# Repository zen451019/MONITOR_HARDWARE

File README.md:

# NEMO: Electromechanical Monitoring Firmware

This repository contains the complete source code for the firmware for NEMO (Node for Electromechanical Monitoring & Operation), a high-performance IoT node designed for real-time monitoring of analog signals.

The system is optimized to capture, process, and transmit voltage and current data from sensors, making it an ideal solution for predictive maintenance, energy consumption monitoring, and industrial machinery diagnostics applications.

## Modbus master monitor documentation

English
https://zen451019.github.io/MONITOR_HARDWARE/28-11-25/English/MASTER_MODBUS/html/index.html

Spanish
https://zen451019.github.io/MONITOR_HARDWARE/28-11-25/Español/MASTER_MODBUS/html/index.html

## Modbus slave monitor documentation
English
https://zen451019.github.io/MONITOR_HARDWARE/28-11-25/English/SLAVE_MODBUS/html/index.html

Spanish
https://zen451019.github.io/MONITOR_HARDWARE/28-11-25/Español/SLAVE_MODBUS/html/index.html

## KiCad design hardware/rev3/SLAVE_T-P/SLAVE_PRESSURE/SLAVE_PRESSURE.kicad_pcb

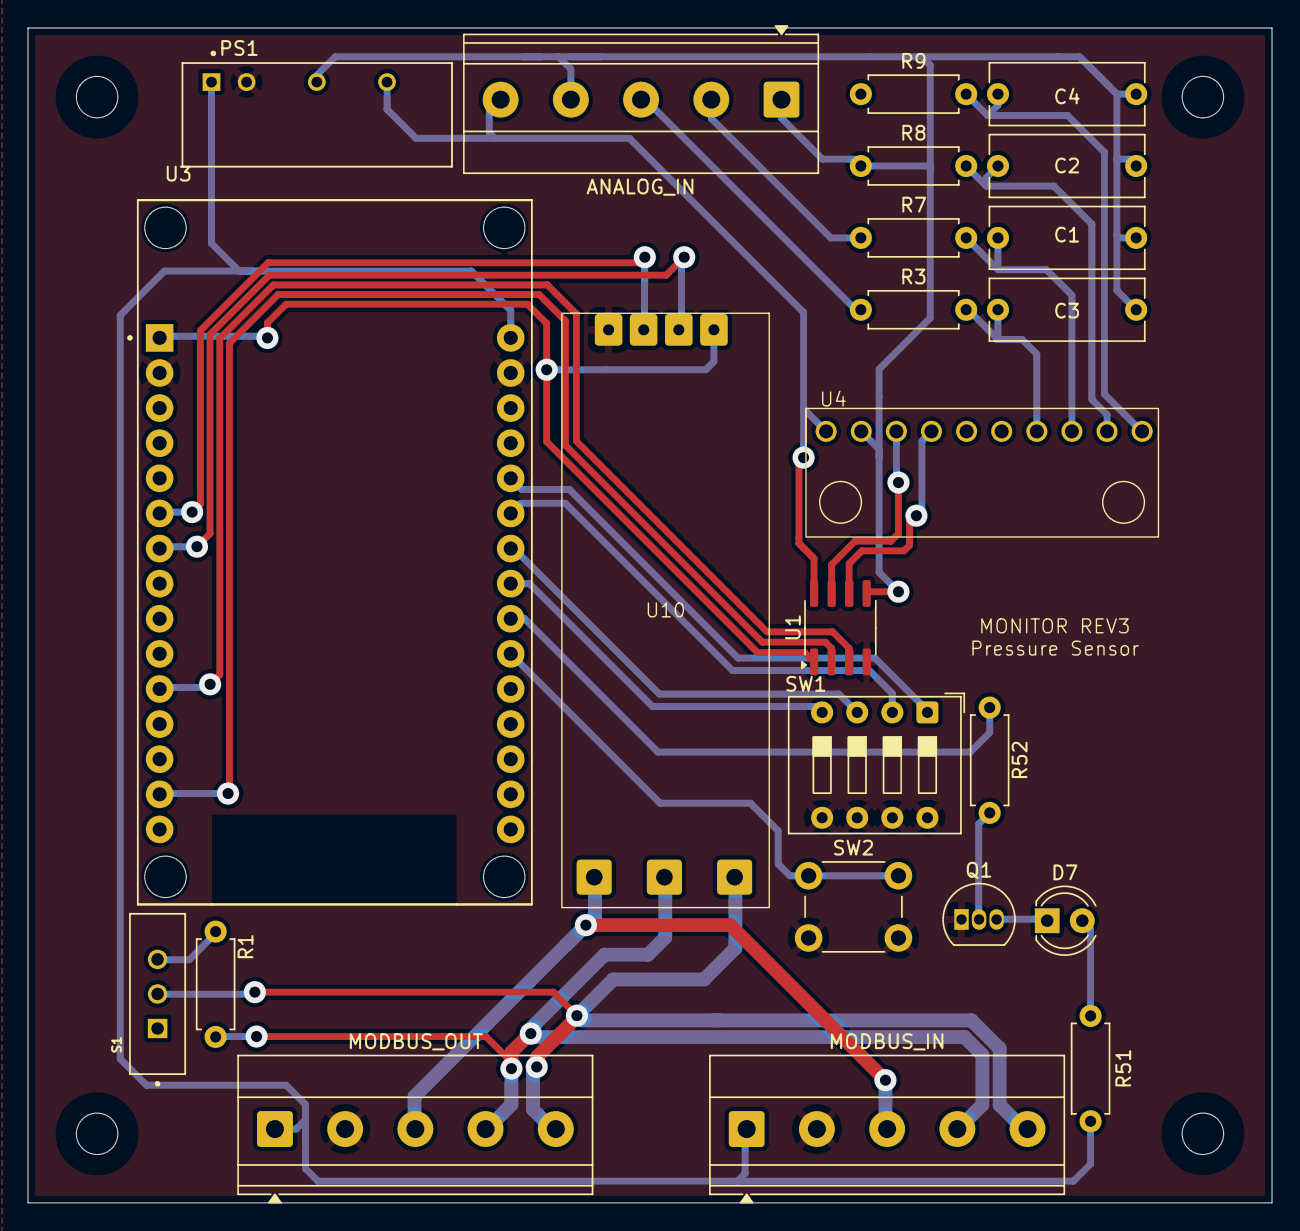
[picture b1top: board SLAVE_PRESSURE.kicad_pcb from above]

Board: 2 copper layers, 90.0 x 85.0 mm, 24 parts (0 on the bottom side), 31 nets.

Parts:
ANALOG_IN: SCREW_TERMINAL_5; TerminalBlock_Phoenix_MKDS-1,5-5-5.08_1x05_P5.08mm_Horizont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
C1, C2, C3, C4: 100nF; C_Rect_L11.0mm_W4.3mm_P10.00mm_MKT
D7: LED; LED_D4.0mm
MODBUS_IN: SCREW_TERMINAL_5; TerminalBlock_Phoenix_MKDS-1,5-5-5.08_1x05_P5.08mm_Horizont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
MODBUS_OUT: SCREW_TEMINAL_5; TerminalBlock_Phoenix_MKDS-1,5-5-5.08_1x05_P5.08mm_Horizont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
PS1: TMH_0505S; CONV_TMH_0505S
Q1: PN2222A; TO-92_Inline
R1, R51: 330; R_Axial_DIN0207_L6.3mm_D2.5mm_P7.62mm_Horizontal
R3, R7, R8, R9: 1K; R_Axial_DIN0207_L6.3mm_D2.5mm_P7.62mm_Horizontal
R52: 3.3k; R_Axial_DIN0207_L6.3mm_D2.5mm_P7.62mm_Horizontal
S1: MINI-SPDT-SW; SW_MINI-SPDT-SW
SW1: SW_DIP_x04; SW_DIP_SPSTx04_Slide_9.78x12.34mm_W7.62mm_P2.54mm
SW2: SW_Push; SW_PUSH_6mm
U1: ADuM1201AR; SOIC-8_3.9x4.9mm_P1.27mm
U3: ESP32-DEVKIT-V1; MODULE_ESP32_DEVKIT_V1
U4: ADS1015
U10: RS485_TRANSCEIVER; XY-017

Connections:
3V3: U1.1 (VDD1), U3.1 (3V3), U10.1 (VCC)
5V: MODBUS_IN.1, MODBUS_OUT.1, PS1.1 (+VIN(VCC)), R51.1, U3.30 (VIN)
5V_ISO: ANALOG_IN.5, PS1.6 (+VOUT), U1.8 (VDD2), U4.8 (VDD)
485+: MODBUS_IN.5, MODBUS_OUT.5, S1.2, U10.5 (A)
485-: MODBUS_IN.4, MODBUS_OUT.4, R1.2, U10.6 (B)
BUTTOM: SW2.1, U3.21 (D32)
DIP_1: SW1.1, U3.26 (D14)
DIP_2: SW1.2, U3.25 (D27)
DIP_3: SW1.3, U3.24 (D26)
DIP_4: SW1.4, U3.23 (D25)
GND: MODBUS_IN.2, MODBUS_OUT.2, PS1.2 (-VIN(GND)), Q1.1 (E), SW1.5, SW1.6, SW1.7, SW1.8, SW2.2, U1.4 (GND1), U3.2 (GND), U3.29 (GND), U10.4 (GND)
GND_ISO: ANALOG_IN.4, C1.1, C2.1, C3.1, C4.1, PS1.4 (-VOUT), U1.5 (GND2), U4.3 (GND)
GND_T: MODBUS_IN.3, MODBUS_OUT.3, U10.7 (GND)
LED: R52.2, U3.22 (D33)
unnamed: D7.2 (A), R51.2
unnamed: D7.1 (K), Q1.3 (C)
unnamed: Q1.2 (B), R52.1
unnamed: R1.1, S1.3
RX: U3.6 (RX2), U10.3 (RXD)
SCL: U1.2 (VOA), U3.14 (D22)
SCL_H: U1.7 (VIA), U4.10 (SCL)
SDA: U1.3 (VIB), U3.11 (D21)
SDA_H: U1.6 (VOB), U4.9 (SDA)
SIGNAL_1: ANALOG_IN.3, R3.1
SIGNAL_2: ANALOG_IN.2, R7.1
SIGNAL_3: ANALOG_IN.1, R8.1
SIGNAL_OUT1: C3.2, R3.2, U4.4 (AIN0)
SIGNAL_OUT2: C1.2, R7.2, U4.5 (AIN1)
SIGNAL_OUT3: C2.2, R8.2, U4.6 (AIN2)
SIGNAL_OUT4: C4.2, R9.2, U4.7 (AIN3)
TX: U3.7 (TX2), U10.2 (TXD)

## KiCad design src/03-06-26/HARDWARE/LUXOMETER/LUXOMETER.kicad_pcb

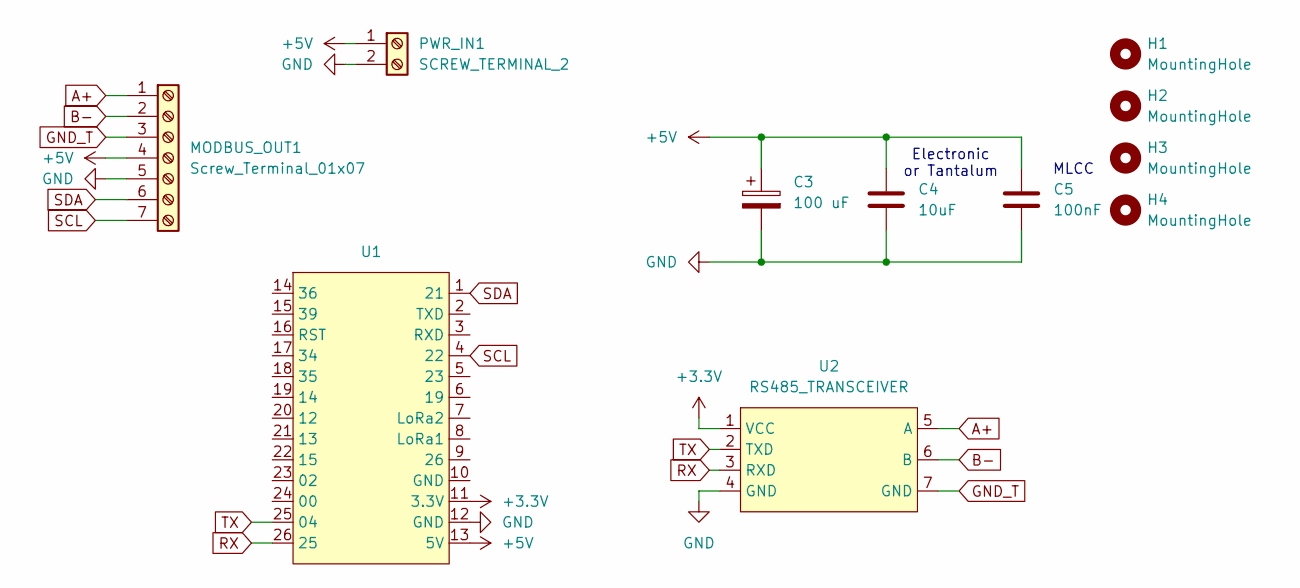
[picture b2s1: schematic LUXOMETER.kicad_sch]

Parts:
C3: 100 uF; CP_Radial_D8.0mm_P5.00mm
C4: 10uF; C_Disc_D7.5mm_W5.0mm_P5.00mm
C5: 100nF; C_Disc_D5.0mm_W2.5mm_P2.50mm
H1, H2, H3, H4: MountingHole; MountingHole_3.2mm_M3
MODBUS_OUT1: Screw_Terminal_01x07; TerminalBlock_Phoenix_MKDS-1,5-7-5.08_1x07_P5.08mm_Horizont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
PWR_IN1: SCREW_TERMINAL_2; TerminalBlock_Phoenix_MKDS-1,5-2-5.08_1x02_P5.08mm_Horizont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
U1: ttgo_lora32
U2: RS485_TRANSCEIVER; XY-017

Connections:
+3.3V: U1.11 (3.3V), U2.1 (VCC)
+5V: C3.1, C4.1, C5.1, MODBUS_OUT1.4, PWR_IN1.1, U1.13 (5V)
A+: MODBUS_OUT1.1, U2.5 (A)
B-: MODBUS_OUT1.2, U2.6 (B)
GND: C3.2, C4.2, C5.2, MODBUS_OUT1.5, PWR_IN1.2, U1.12 (GND), U2.4 (GND)
GND_T: MODBUS_OUT1.3, U2.7 (GND)
RX: U1.26 (25), U2.3 (RXD)
SCL: MODBUS_OUT1.7, U1.4 (22)
SDA: MODBUS_OUT1.6, U1.1 (21)
TX: U1.25 (04), U2.2 (TXD)

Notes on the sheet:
Electronic or Tantalum
MLCC

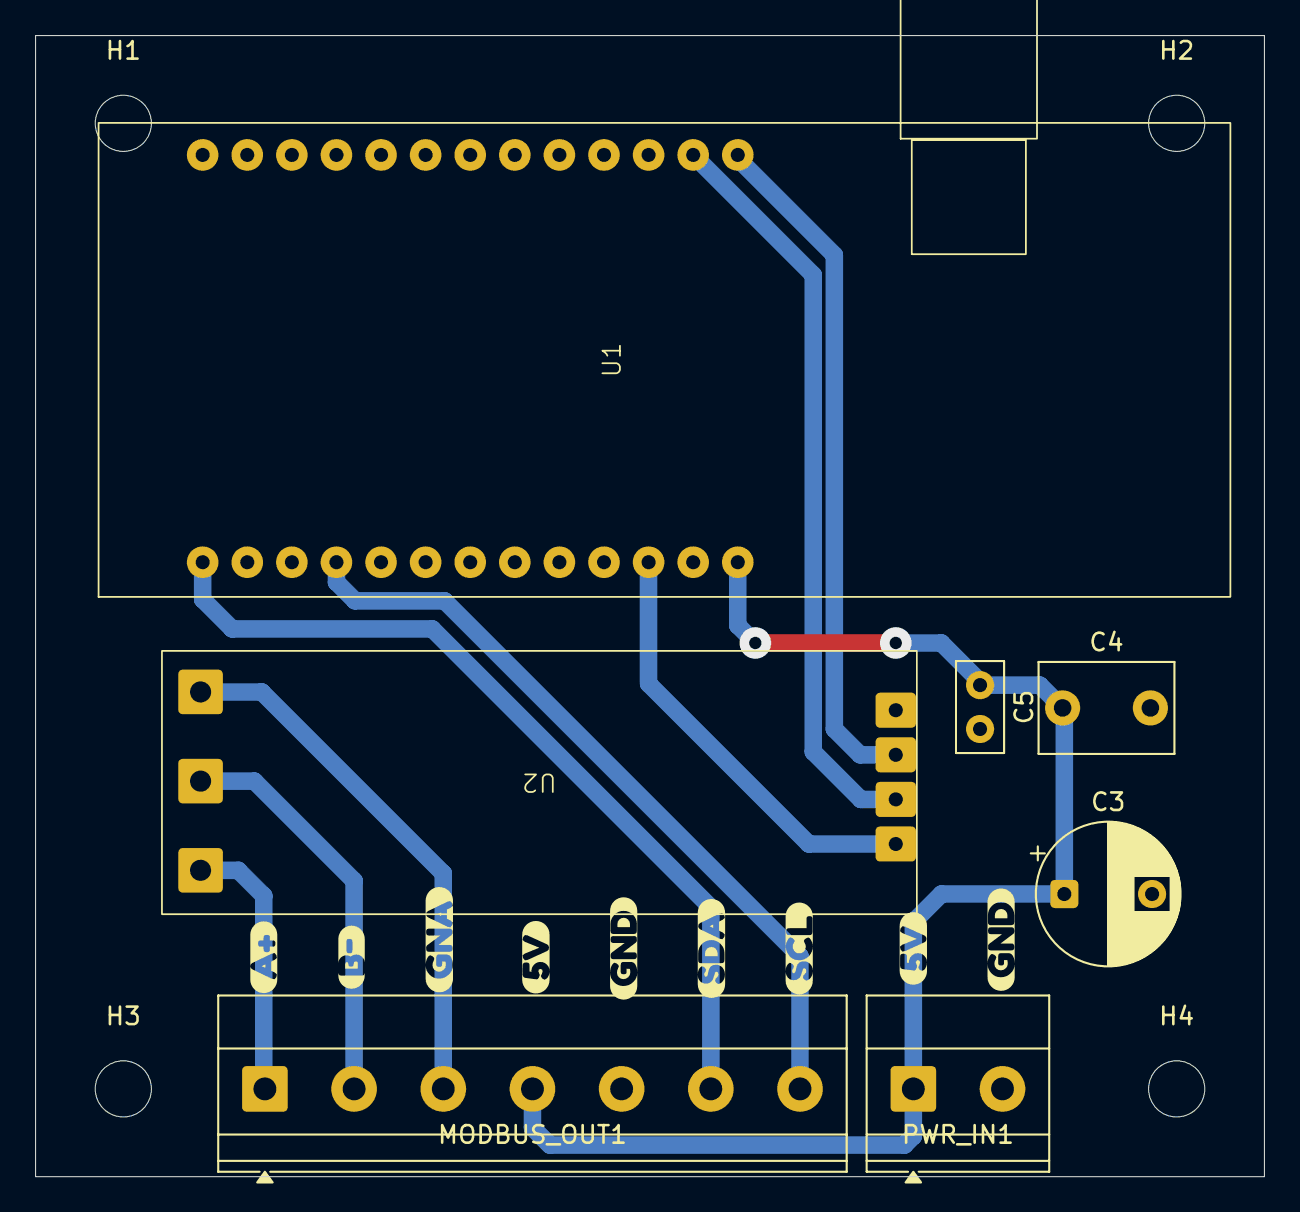
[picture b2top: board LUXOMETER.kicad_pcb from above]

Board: 2 copper layers, 70.0 x 65.0 mm, 20 parts (0 on the bottom side), 10 nets.

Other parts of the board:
kibuzzard-6A2423AA: G***; kibuzzard-6A2423AA
kibuzzard-6A2423C2: G***; kibuzzard-6A2423C2
kibuzzard-6A2424E2: G***; kibuzzard-6A2424E2
kibuzzard-6A2424EE, kibuzzard-6A2424EE#2: G***; kibuzzard-6A2424EE
kibuzzard-6A2424FA, kibuzzard-6A2424FA#2: G***; kibuzzard-6A2424FA
kibuzzard-6A24251B: G***; kibuzzard-6A24251B
kibuzzard-6A24252A: G***; kibuzzard-6A24252A

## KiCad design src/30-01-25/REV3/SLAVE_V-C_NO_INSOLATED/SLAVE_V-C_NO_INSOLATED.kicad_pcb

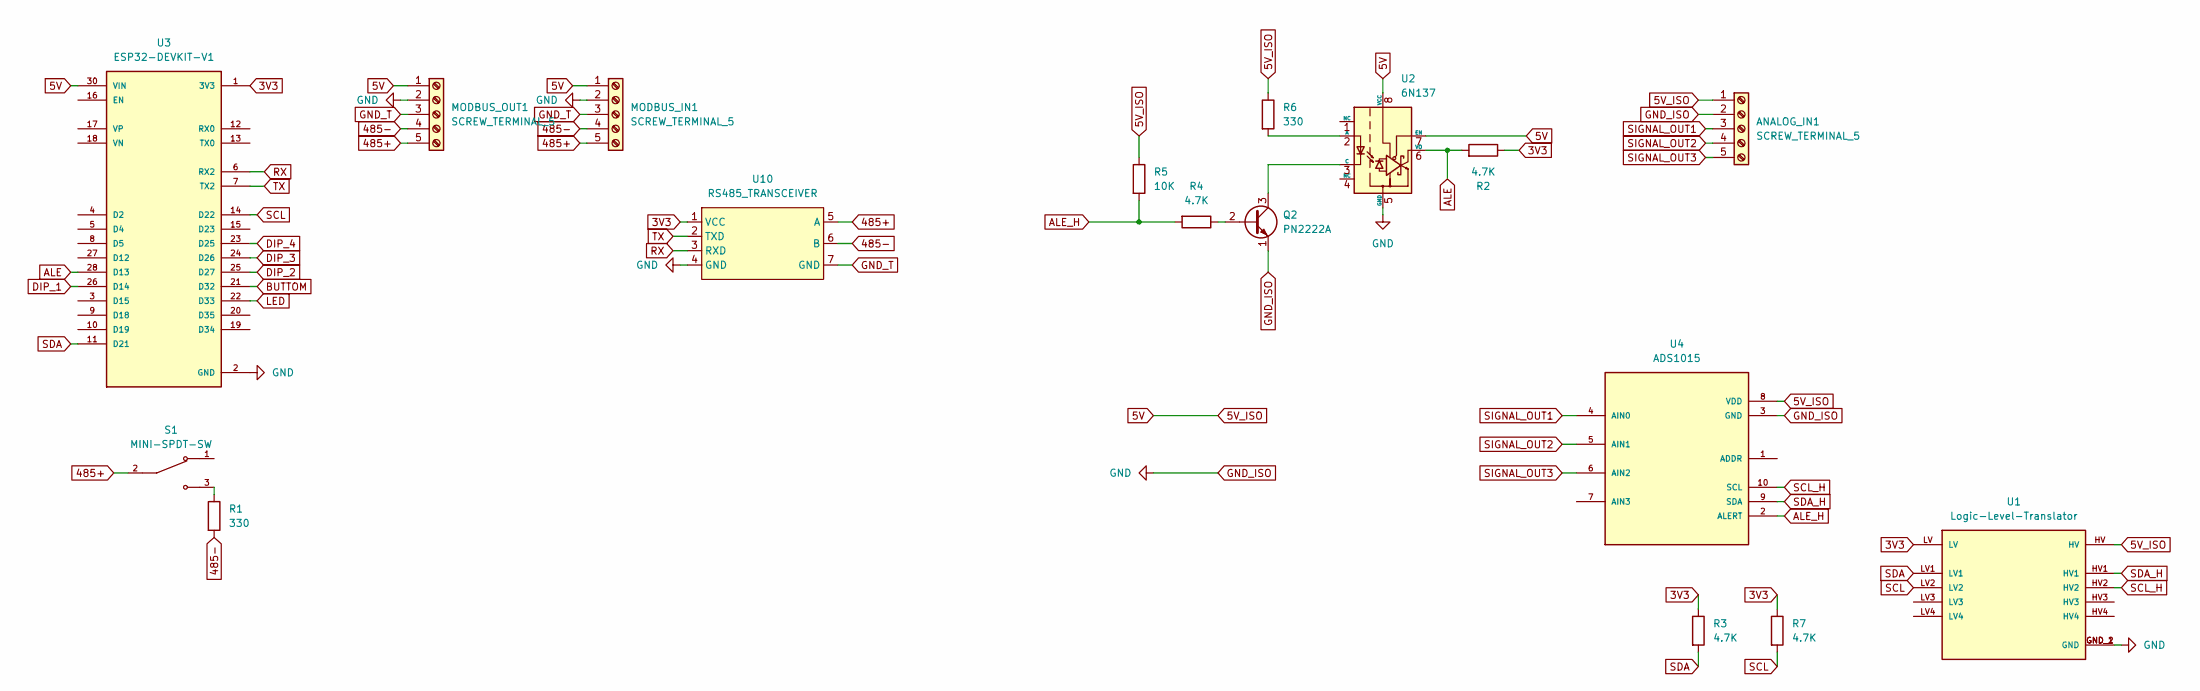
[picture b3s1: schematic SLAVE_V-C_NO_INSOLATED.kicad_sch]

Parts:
ANALOG_IN1: SCREW_TERMINAL_5; TerminalBlock_Phoenix_MKDS-1,5-5-5.08_1x05_P5.08mm_Horizont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
MODBUS_IN1: SCREW_TERMINAL_5; TerminalBlock_Phoenix_MKDS-1,5-5-5.08_1x05_P5.08mm_Horizont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
MODBUS_OUT1: SCREW_TERMINAL_5; TerminalBlock_Phoenix_MKDS-1,5-5-5.08_1x05_P5.08mm_Horizont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
Q2: PN2222A; TO-92_Inline
R1, R6: 330; R_Axial_DIN0207_L6.3mm_D2.5mm_P7.62mm_Horizontal
R2, R3, R4, R7: 4.7K; R_Axial_DIN0207_L6.3mm_D2.5mm_P7.62mm_Horizontal
R5: 10K; R_Axial_DIN0207_L6.3mm_D2.5mm_P7.62mm_Horizontal
S1: MINI-SPDT-SW; SW_MINI-SPDT-SW
U1: Logic-Level-Translator; CONV_BOB-12009
U2: 6N137; DIP-8_W7.62mm
U3: ESP32-DEVKIT-V1; MODULE_ESP32_DEVKIT_V1; PARTREV N/A
U4: ADS1015
U10: RS485_TRANSCEIVER; XY-017

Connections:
3V3: R2.1, R3.1, R7.1, U1.LV, U3.1 (3V3), U10.1 (VCC)
5V: ANALOG_IN1.1, MODBUS_IN1.1, MODBUS_OUT1.1, R5.1, R6.1, U1.HV, U2.7 (EN), U2.8 (VCC), U3.30 (VIN), U4.8 (VDD)
485+: MODBUS_IN1.5, MODBUS_OUT1.5, S1.2, U10.5 (A)
485-: MODBUS_IN1.4, MODBUS_OUT1.4, R1.2, U10.6 (B)
ALE: R2.2, U2.6 (VO), U3.28 (D13)
ALE_H: R4.2, R5.2, U4.2 (ALERT)
BUTTOM: U3.21 (D32)
DIP_1: U3.26 (D14)
DIP_2: U3.25 (D27)
DIP_3: U3.24 (D26)
DIP_4: U3.23 (D25)
GND_ISO: ANALOG_IN1.2, MODBUS_IN1.2, MODBUS_OUT1.2, Q2.1 (E), U1.GND_1 (GND), U1.GND_2 (GND), U2.5 (GND), U3.2 (GND), U3.29 (GND), U4.3 (GND), U10.4 (GND)
GND_T: MODBUS_IN1.3, MODBUS_OUT1.3, U10.7 (GND)
LED: U3.22 (D33)
unnamed: Q2.2 (B), R4.1
unnamed: Q2.3 (C), U2.3 (C)
unnamed: R1.1, S1.3
unnamed: R6.2, U2.2 (A)
RX: U3.6 (RX2), U10.3 (RXD)
SCL: R7.2, U1.LV2, U3.14 (D22)
SCL_H: U1.HV2, U4.10 (SCL)
SDA: R3.2, U1.LV1, U3.11 (D21)
SDA_H: U1.HV1, U4.9 (SDA)
SIGNAL_OUT1: ANALOG_IN1.3, U4.4 (AIN0)
SIGNAL_OUT2: ANALOG_IN1.4, U4.5 (AIN1)
SIGNAL_OUT3: ANALOG_IN1.5, U4.6 (AIN2)
TX: U3.7 (TX2), U10.2 (TXD)

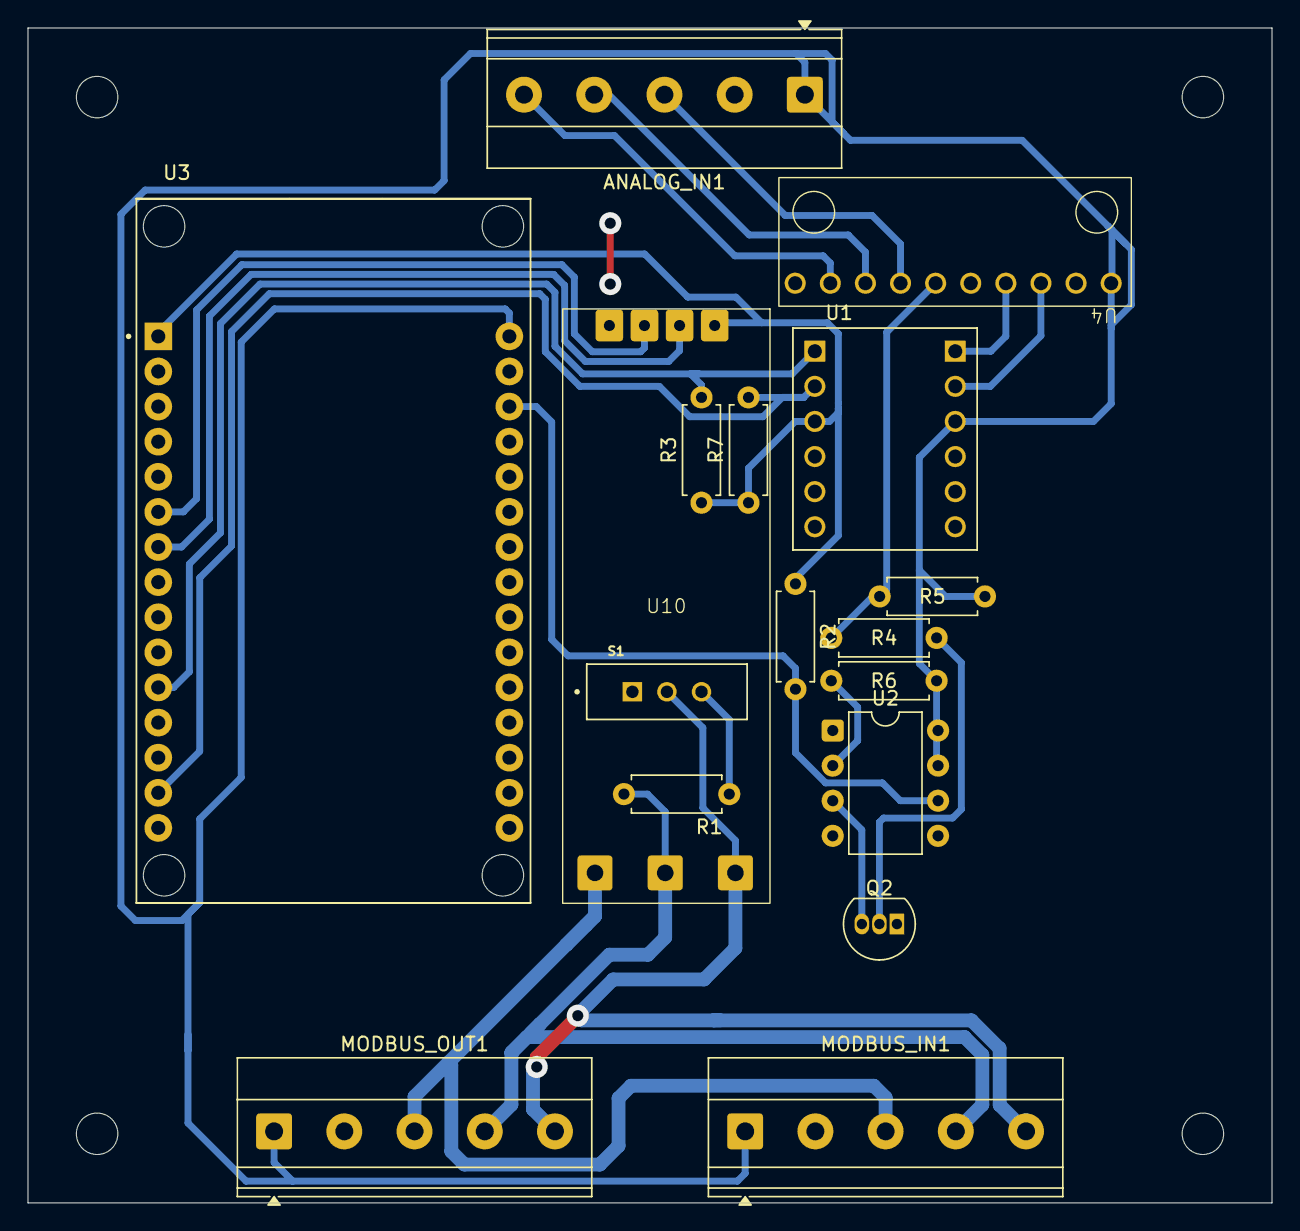
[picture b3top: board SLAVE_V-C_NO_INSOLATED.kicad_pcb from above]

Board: 2 copper layers, 90.0 x 85.0 mm, 17 parts (0 on the bottom side), 21 nets.

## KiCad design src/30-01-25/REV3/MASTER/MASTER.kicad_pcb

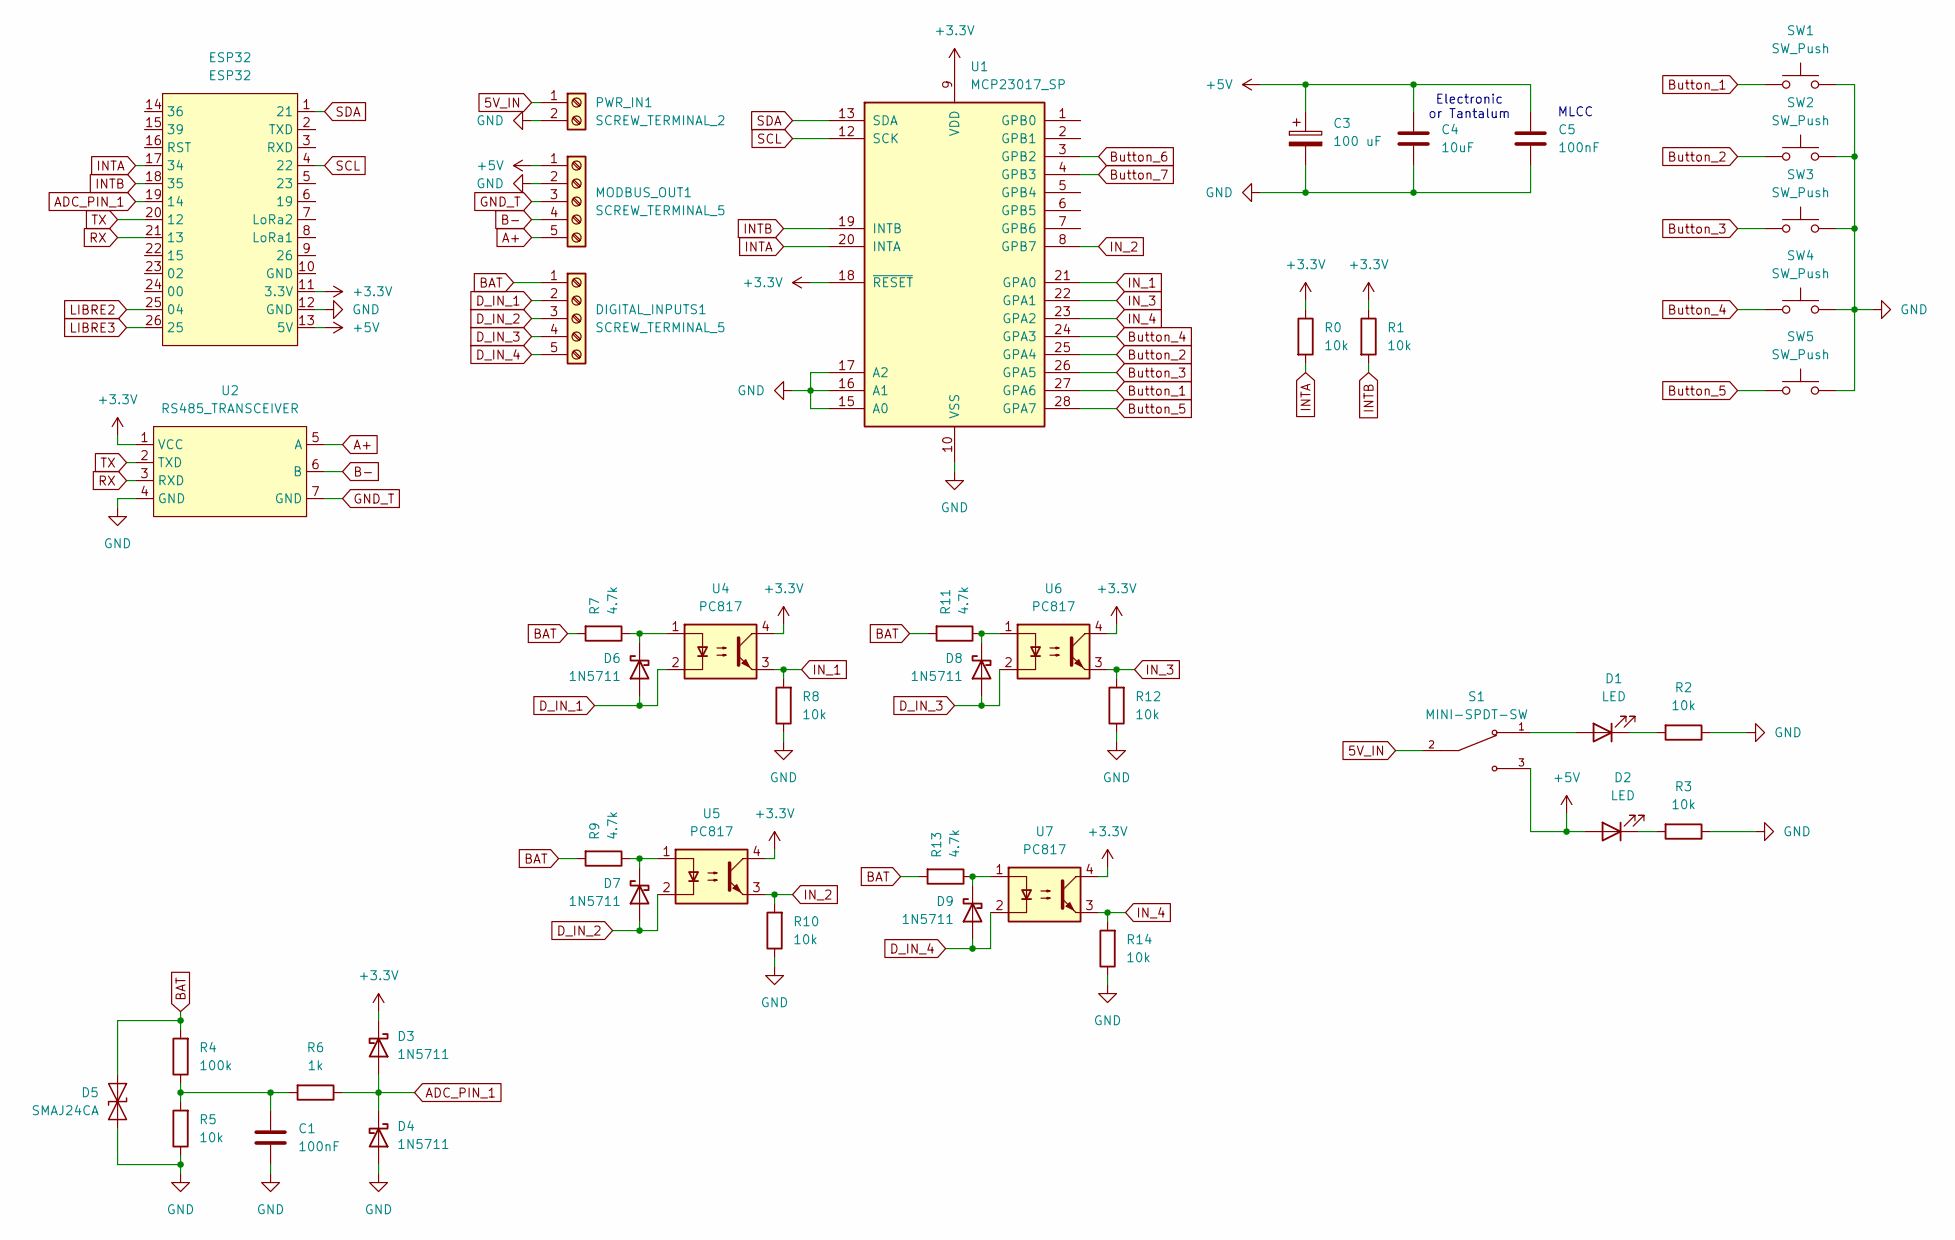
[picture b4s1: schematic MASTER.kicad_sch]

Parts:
C1, C5: 100nF; C_Disc_D5.0mm_W2.5mm_P2.50mm
C3: 100 uF; CP_Radial_D8.0mm_P5.00mm
C4: 10uF; C_Disc_D7.5mm_W5.0mm_P5.00mm
D1, D2: LED; LED_D5.0mm
D3, D4, D6, D7, D8, D9: 1N5711; D_DO-35_SOD27_P7.62mm_Horizontal
D5: SMAJ24CA; D_SMA
DIGITAL_INPUTS1: SCREW_TERMINAL_5; TerminalBlock_Phoenix_MKDS-1,5-5-5.08_1x05_P5.08mm_Horizont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
ESP32: ESP32; ttgo_lora32
MODBUS_OUT1: SCREW_TERMINAL_5; TerminalBlock_Phoenix_MKDS-1,5-5-5.08_1x05_P5.08mm_Horizont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
PWR_IN1: SCREW_TERMINAL_2; TerminalBlock_Phoenix_MKDS-1,5-2-5.08_1x02_P5.08mm_Horizont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
R0, R1, R2, R3, R5, R8, R10, R12, R14: 10k; R_Axial_DIN0207_L6.3mm_D2.5mm_P7.62mm_Horizontal
R4: 100k; R_Axial_DIN0207_L6.3mm_D2.5mm_P7.62mm_Horizontal
R6: 1k; R_Axial_DIN0207_L6.3mm_D2.5mm_P7.62mm_Horizontal
R7, R9, R11, R13: 4.7k; R_Axial_DIN0207_L6.3mm_D2.5mm_P7.62mm_Horizontal
S1: MINI-SPDT-SW; SW_MINI-SPDT-SW
SW1, SW2, SW3, SW4, SW5: SW_Push; SW_PUSH_6mm
U1: MCP23017_SP; DIP-28_W7.62mm_LongPads
U2: RS485_TRANSCEIVER; XY-017
U4, U5, U6, U7: PC817; DIP-4_W7.62mm

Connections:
5V_IN: PWR_IN1.1, S1.2
+3.3V: D3.1 (K), ESP32.11 (3.3V), R0.1, R1.1, U1.9 (VDD), U1.18 (~RESET), U2.1 (VCC), U4.4, U5.4, U6.4, U7.4
+5V: C3.1, C4.1, C5.1, D2.2 (A), ESP32.13 (5V), MODBUS_OUT1.1, S1.3
A+: MODBUS_OUT1.5, U2.5 (A)
ADC_PIN_1: D3.2 (A), D4.1 (K), ESP32.19 (14), R6.1
B-: MODBUS_OUT1.4, U2.6 (B)
BAT: D5.2 (A2), DIGITAL_INPUTS1.1, R4.2, R7.2, R9.2, R11.2, R13.2
Button_1: SW1.1, U1.27 (GPA6)
Button_2: SW2.1, U1.25 (GPA4)
Button_3: SW3.1, U1.26 (GPA5)
Button_4: SW4.1, U1.24 (GPA3)
Button_5: SW5.1, U1.28 (GPA7)
Button_6: U1.3 (GPB2)
Button_7: U1.4 (GPB3)
D_IN_1: D6.2 (A), DIGITAL_INPUTS1.2, U4.2
D_IN_2: D7.2 (A), DIGITAL_INPUTS1.3, U5.2
D_IN_3: D8.2 (A), DIGITAL_INPUTS1.4, U6.2
D_IN_4: D9.2 (A), DIGITAL_INPUTS1.5, U7.2
GND: C1.2, C3.2, C4.2, C5.2, D4.2 (A), D5.1 (A1), ESP32.12 (GND), MODBUS_OUT1.2, PWR_IN1.2, R2.1, R3.1, R5.1, R8.1, R10.1, R12.1, R14.1, SW1.2, SW2.2, SW3.2, SW4.2, SW5.2, U1.10 (VSS), U1.15 (A0), U1.16 (A1), U1.17 (A2), U2.4 (GND)
GND_T: MODBUS_OUT1.3, U2.7 (GND)
INTA: ESP32.17 (34), R0.2, U1.20 (INTA)
INTB: ESP32.18 (35), R1.2, U1.19 (INTB)
IN_1: R8.2, U1.21 (GPA0), U4.3
IN_2: R10.2, U1.8 (GPB7), U5.3
IN_3: R12.2, U1.22 (GPA1), U6.3
IN_4: R14.2, U1.23 (GPA2), U7.3
LIBRE2: ESP32.25 (04)
LIBRE3: ESP32.26 (25)
unnamed: C1.1, R4.1, R5.2, R6.2
unnamed: D1.2 (A), S1.1
unnamed: D1.1 (K), R2.2
unnamed: D2.1 (K), R3.2
unnamed: D6.1 (K), R7.1, U4.1
unnamed: D7.1 (K), R9.1, U5.1
unnamed: D8.1 (K), R11.1, U6.1
unnamed: D9.1 (K), R13.1, U7.1
RX: ESP32.21 (13), U2.3 (RXD)
SCL: ESP32.4 (22), U1.12 (SCK)
SDA: ESP32.1 (21), U1.13 (SDA)
TX: ESP32.20 (12), U2.2 (TXD)

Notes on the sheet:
MLCC
Electronic or Tantalum

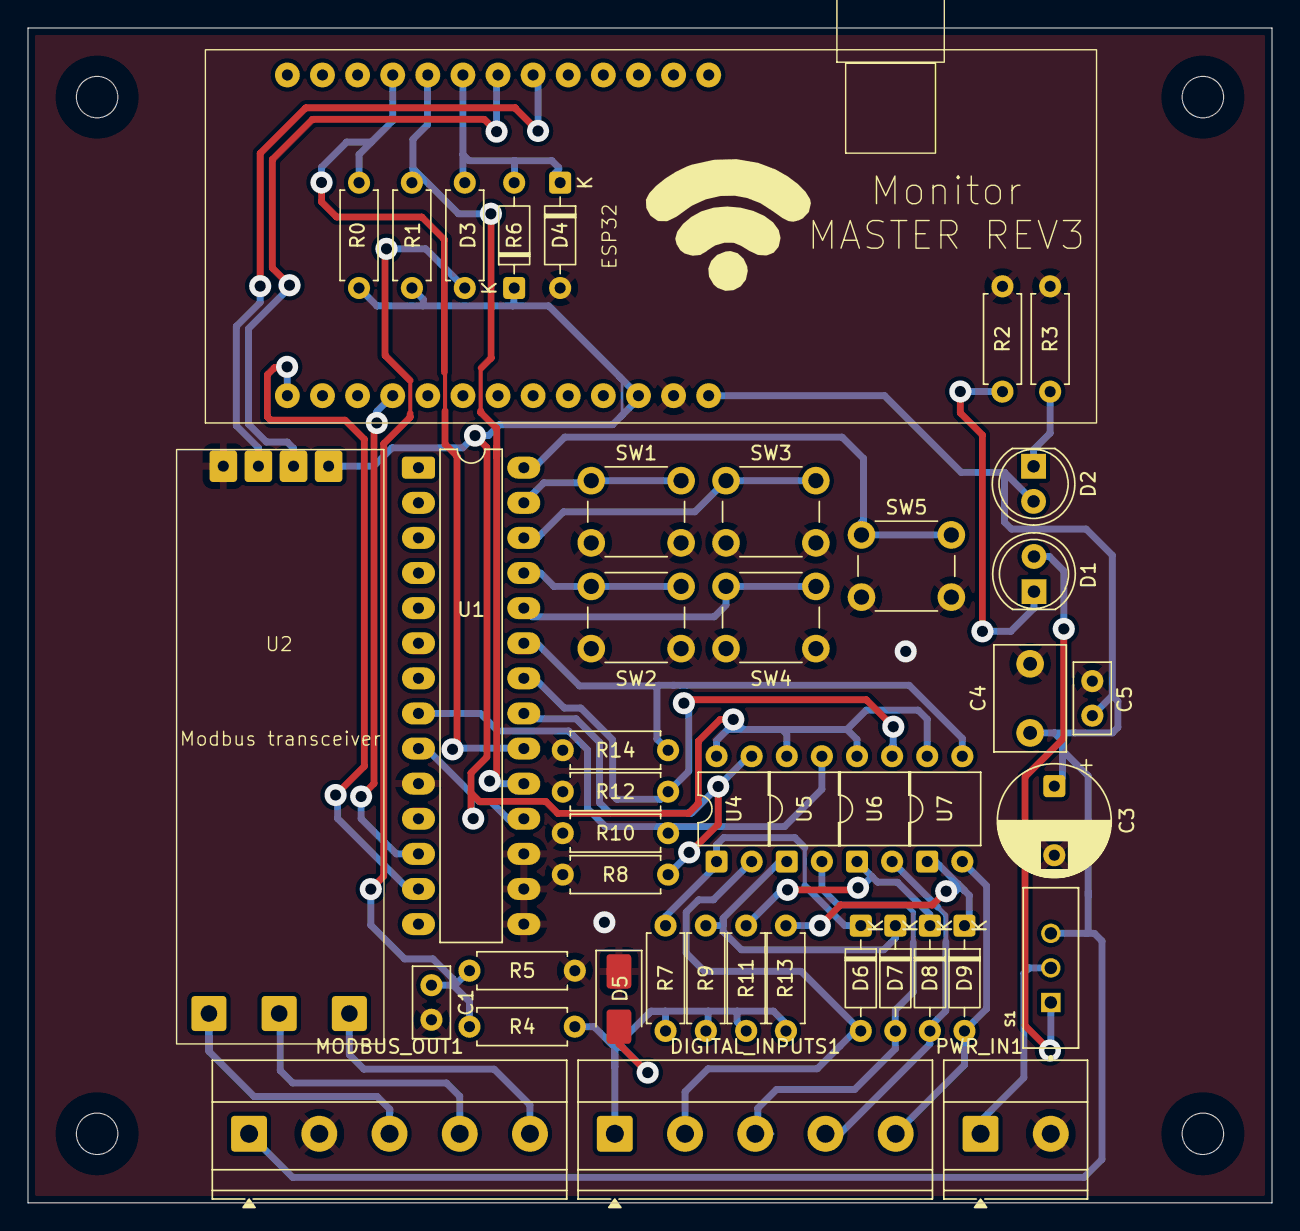
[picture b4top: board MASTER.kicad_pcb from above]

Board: 2 copper layers, 90.0 x 85.0 mm, 44 parts (0 on the bottom side), 36 nets.

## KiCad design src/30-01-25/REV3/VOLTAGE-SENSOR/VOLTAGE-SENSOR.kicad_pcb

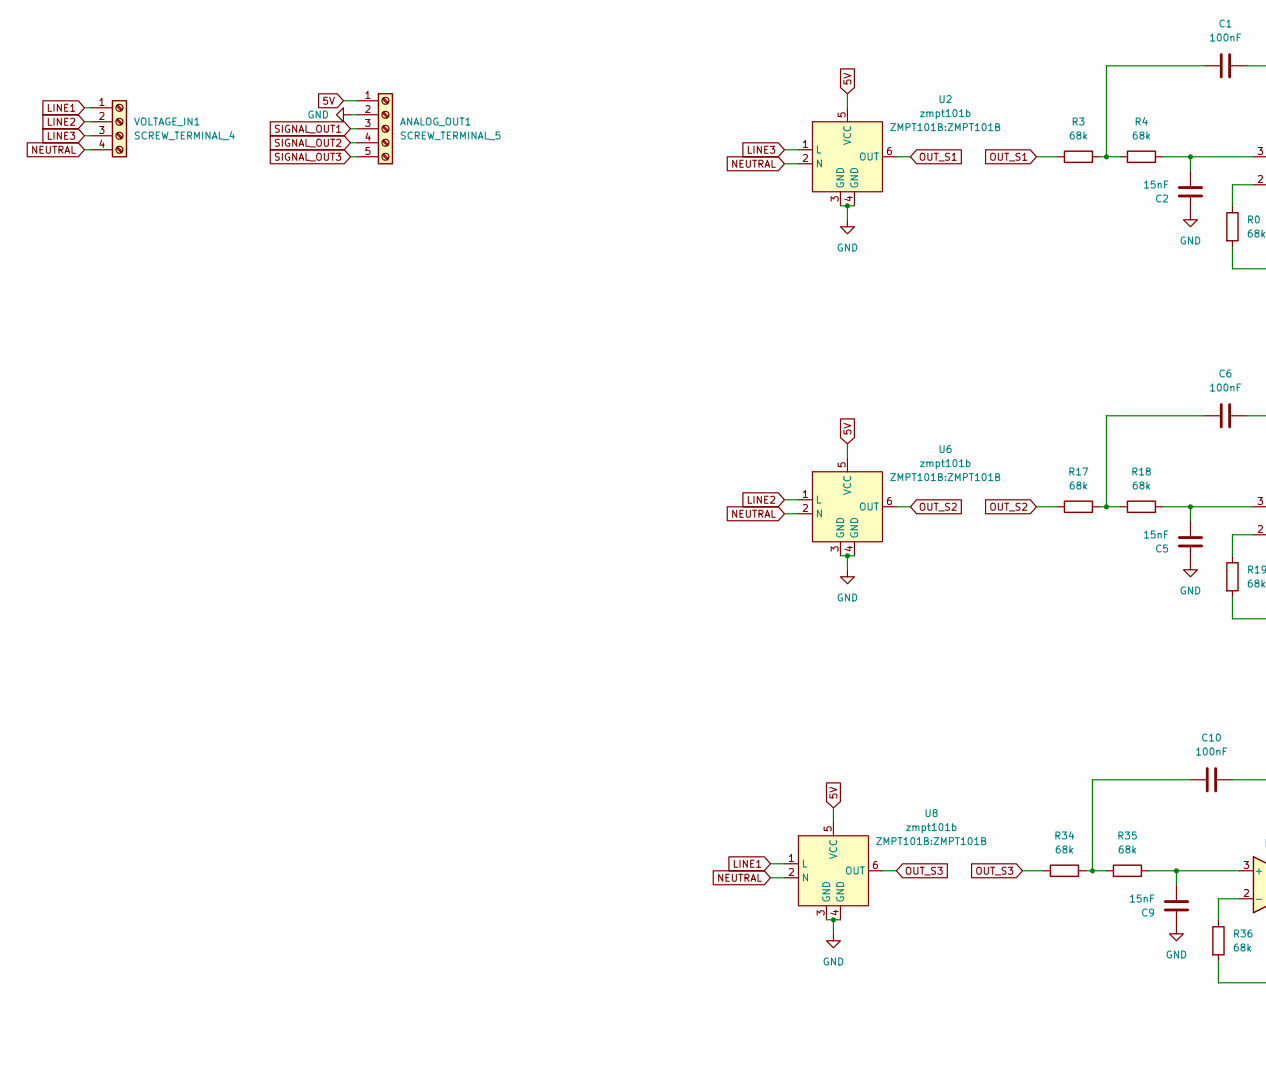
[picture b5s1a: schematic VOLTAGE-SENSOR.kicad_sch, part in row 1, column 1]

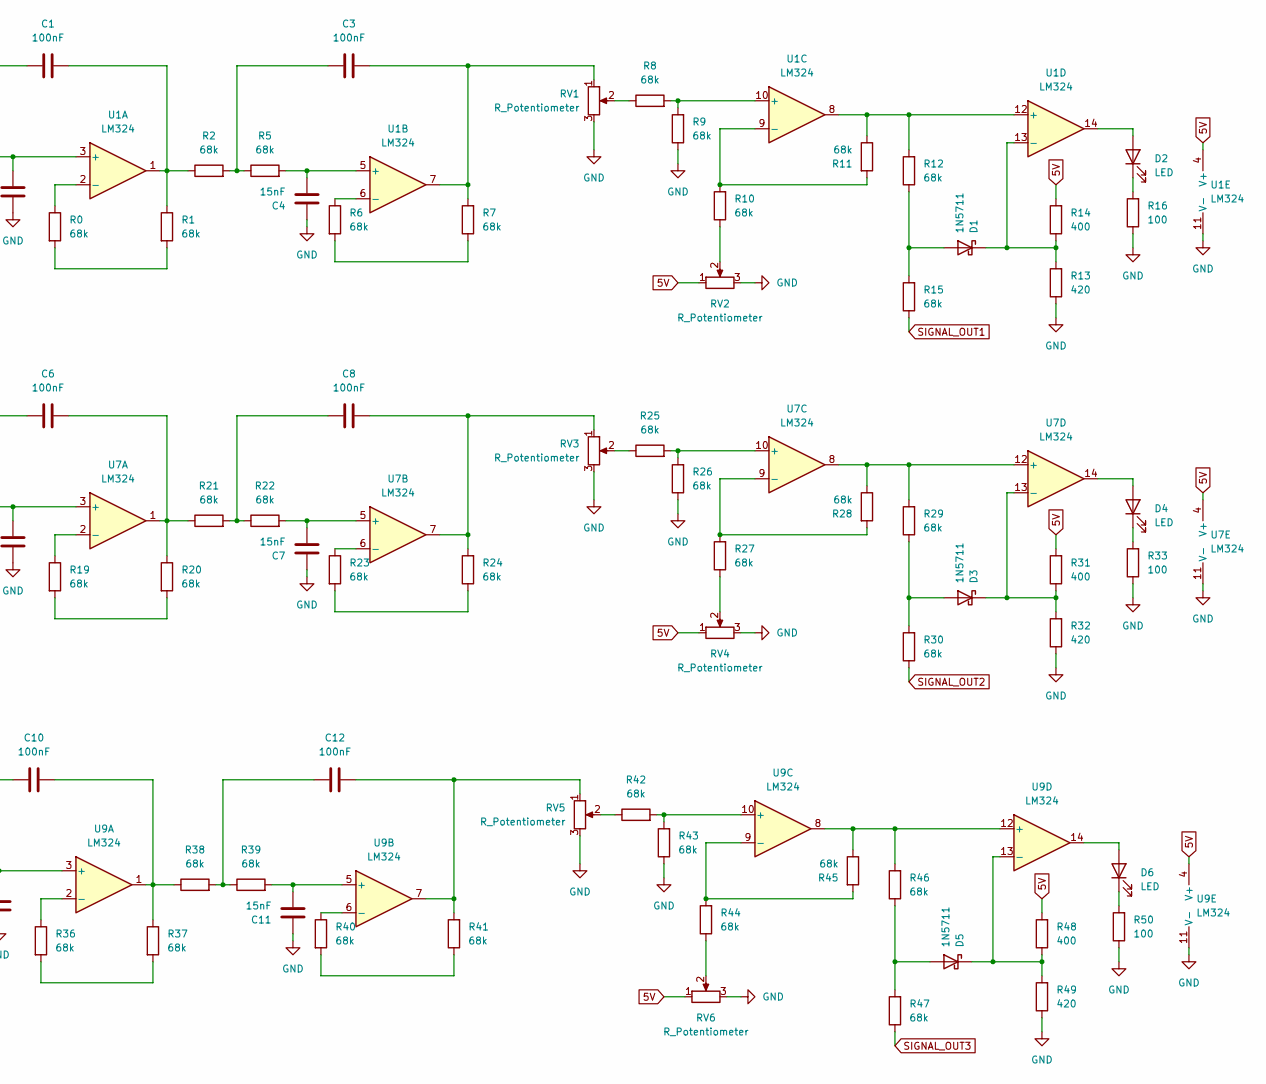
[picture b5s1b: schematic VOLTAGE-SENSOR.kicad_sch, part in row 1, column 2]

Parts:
ANALOG_OUT1: SCREW_TERMINAL_5; TerminalBlock_Phoenix_MKDS-1,5-5-5.08_1x05_P5.08mm_Horizont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
C1, C3, C6, C8, C10, C12: 100nF; C_Rect_L11.0mm_W4.3mm_P10.00mm_MKT
C2, C4, C5, C7, C9, C11: 15nF; C_Rect_L7.0mm_W2.5mm_P5.00mm
D1, D3, D5: 1N5711; D_DO-35_SOD27_P7.62mm_Horizontal
D2, D4, D6: LED; LED_D4.0mm
R0, R1, R2, R3, R4, R5, R6, R7, R8, R9, R10, R11, R12, R15, R17, R18, R19, R20, R21, R22, R23, R24, R25, R26, R27, R28, R29, R30, R34, R35, R36, R37, R38, R39, R40, R41, R42, R43, R44, R45, R46, R47: 68k; R_Axial_DIN0207_L6.3mm_D2.5mm_P7.62mm_Horizontal
R13, R32, R49: 420; R_Axial_DIN0207_L6.3mm_D2.5mm_P7.62mm_Horizontal
R14, R31, R48: 400; R_Axial_DIN0207_L6.3mm_D2.5mm_P7.62mm_Horizontal
R16, R33, R50: 100; R_Axial_DIN0207_L6.3mm_D2.5mm_P7.62mm_Horizontal
RV1, RV2, RV3, RV4, RV5, RV6: R_Potentiometer; Potentiometer_Bourns_3296W_Vertical
U1, U7, U9: LM324; DIP-14_W7.62mm_LongPads
U2, U6, U8: zmpt101b; ZMPT101B
VOLTAGE_IN1: SCREW_TERMINAL_4; TerminalBlock_Phoenix_MKDS-1,5-4-5.08_1x04_P5.08mm_Horizont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

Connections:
5V: ANALOG_OUT1.1, R14.2, R31.2, R48.2, RV2.1, RV4.1, RV6.1, U1.4 (V+), U2.5 (VCC), U6.5 (VCC), U7.4 (V+), U8.5 (VCC), U9.4 (V+)
GND: ANALOG_OUT1.2, C2.1, C4.1, C5.1, C7.1, C9.1, C11.1, R9.1, R13.1, R16.1, R26.1, R32.1, R33.1, R43.1, R49.1, R50.1, RV1.3, RV2.3, RV3.3, RV4.3, RV5.3, RV6.3, U1.11 (V-), U2.3 (GND), U2.4 (GND), U6.3 (GND), U6.4 (GND), U7.11 (V-), U8.3 (GND), U8.4 (GND), U9.11 (V-)
LINE1: U8.1 (L), VOLTAGE_IN1.1; also elsewhere on the board
LINE2: U6.1 (L), VOLTAGE_IN1.2; also elsewhere on the board
LINE3: U2.1 (L), VOLTAGE_IN1.3; also elsewhere on the board
NEUTRAL: U2.2 (N), U6.2 (N), U8.2 (N), VOLTAGE_IN1.4; also elsewhere on the board
unnamed: C1.1, R3.2, R4.1
unnamed: C1.2, R1.1, R2.1, U1.1
unnamed: C3.1, R2.2, R5.1
unnamed: C3.2, R7.2, RV1.1, U1.7
unnamed: C6.1, R17.2, R18.1
unnamed: C6.2, R20.1, R21.1, U7.1
unnamed: C8.1, R21.2, R22.1
unnamed: C8.2, R24.2, RV3.1, U7.7
unnamed: C10.1, R34.2, R35.1
unnamed: C10.2, R37.1, R38.1, U9.1
unnamed: C12.1, R38.2, R39.1
unnamed: C12.2, R41.2, RV5.1, U9.7
unnamed: D1.2 (A), R12.1, R15.2
unnamed: D1.1 (K), R13.2, R14.1, U1.13 (-)
unnamed: D2.2 (A), U1.14
unnamed: D2.1 (K), R16.2
unnamed: D3.2 (A), R29.1, R30.2
unnamed: D3.1 (K), R31.1, R32.2, U7.13 (-)
unnamed: D4.2 (A), U7.14
unnamed: D4.1 (K), R33.2
unnamed: D5.2 (A), R46.1, R47.2
unnamed: D5.1 (K), R48.1, R49.2, U9.13 (-)
unnamed: D6.2 (A), U9.14
unnamed: D6.1 (K), R50.2
unnamed: R0.2, R1.2
unnamed: R6.2, R7.1
unnamed: R8.1, RV1.2
unnamed: R10.1, RV2.2
unnamed: R19.2, R20.2
unnamed: R23.2, R24.1
unnamed: R25.1, RV3.2
unnamed: R27.1, RV4.2
unnamed: R36.2, R37.2
unnamed: R40.2, R41.1
unnamed: R42.1, RV5.2
unnamed: R44.1, RV6.2
unnamed: C2.2, R4.2, U1.3 (+)
unnamed: R0.1, U1.2 (-)
unnamed: C4.2, R5.2, U1.5 (+)
unnamed: R6.1, U1.6 (-)
unnamed: R8.2, R9.2, U1.10 (+)
unnamed: R10.2, R11.2, U1.9 (-)
unnamed: R11.1, R12.2, U1.8, U1.12 (+)
unnamed: C5.2, R18.2, U7.3 (+)
unnamed: R19.1, U7.2 (-)
unnamed: C7.2, R22.2, U7.5 (+)
unnamed: R23.1, U7.6 (-)
unnamed: R25.2, R26.2, U7.10 (+)
unnamed: R27.2, R28.2, U7.9 (-)
unnamed: R28.1, R29.2, U7.8, U7.12 (+)
unnamed: C9.2, R35.2, U9.3 (+)
unnamed: R36.1, U9.2 (-)
unnamed: C11.2, R39.2, U9.5 (+)
unnamed: R40.1, U9.6 (-)
unnamed: R42.2, R43.2, U9.10 (+)
unnamed: R44.2, R45.2, U9.9 (-)
unnamed: R45.1, R46.2, U9.8, U9.12 (+)
OUT_S1: R3.1, U2.6 (OUT)
OUT_S2: R17.1, U6.6 (OUT)
OUT_S3: R34.1, U8.6 (OUT)
SIGNAL_OUT1: ANALOG_OUT1.3, R15.1
SIGNAL_OUT2: ANALOG_OUT1.4, R30.1
SIGNAL_OUT3: ANALOG_OUT1.5, R47.1
